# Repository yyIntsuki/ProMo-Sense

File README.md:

# ProMo-Sense

This repository is used for development and version control of ProMo-Sense.

### Overview
```bash
ProMo-Sense
├── hardware: hardware components development (audio module, code-lock)
├── raspberry: integration code with hardware components and database on Raspberry Pi (using Python)
├── web: web application code and functionalities including database (using Vite-React)
```

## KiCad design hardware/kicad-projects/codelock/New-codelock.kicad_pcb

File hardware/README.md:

# Raspberry

This folder is designated for hardware components such as their KiCad projects.

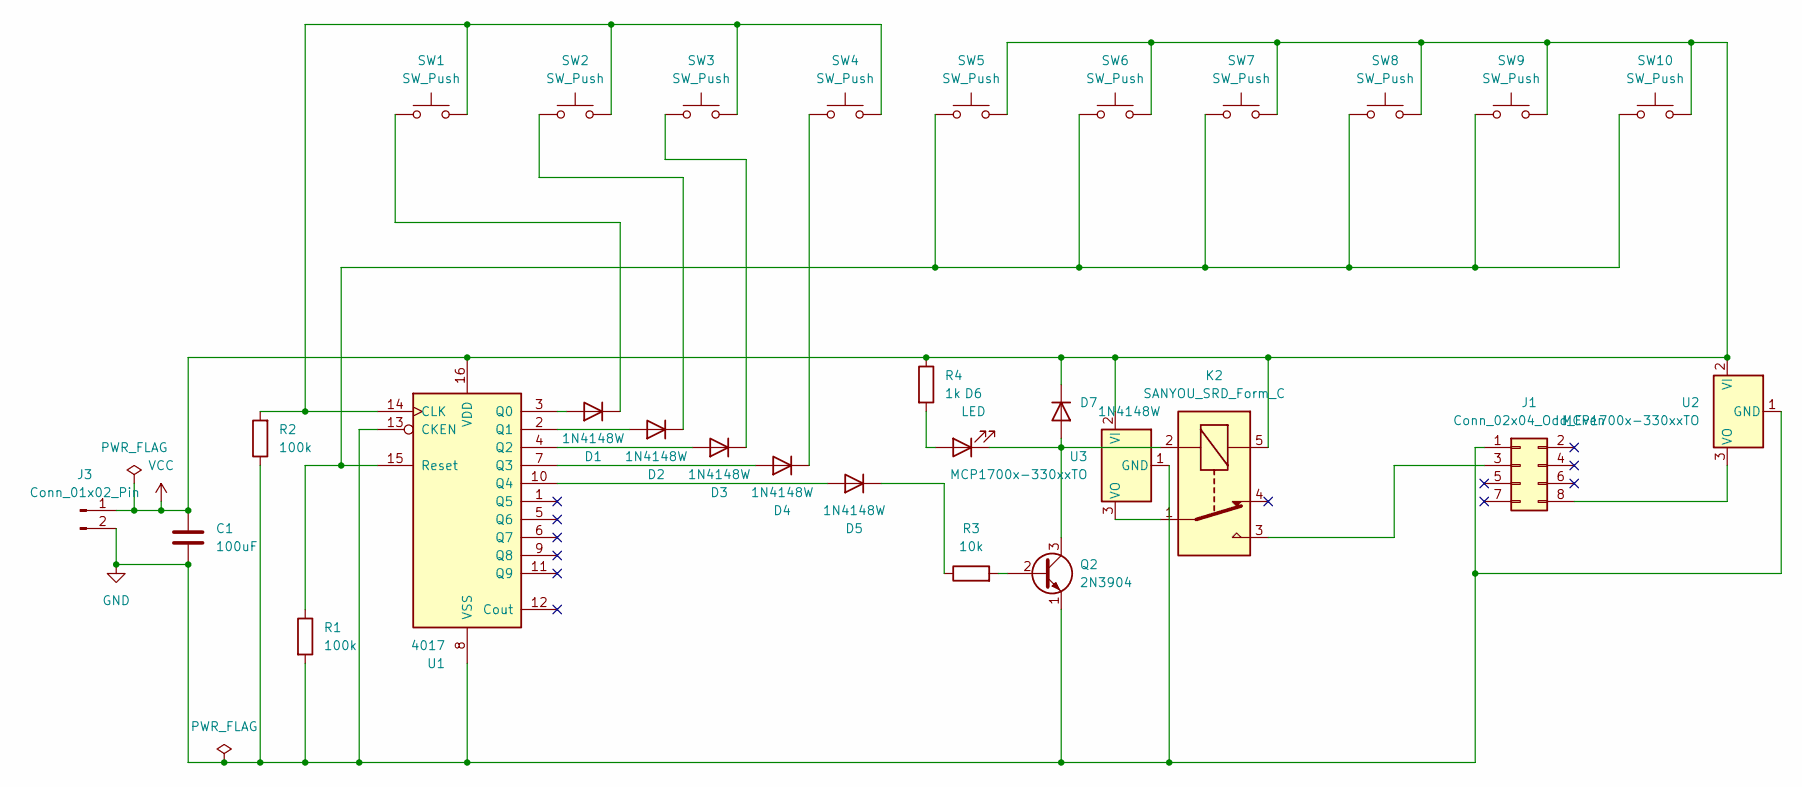
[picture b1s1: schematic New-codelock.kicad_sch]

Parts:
C1: 100uF; C_0805_2012Metric_Pad1.18x1.45mm_HandSolder
D1, D2, D3, D4, D5, D7: 1N4148W; D_SOD-123
D6: LED; LED_D5.0mm
J1: Conn_02x04_Odd_Even; PinSocket_2x04_P2.54mm_Vertical
J3: Conn_01x02_Pin; PinHeader_1x02_P2.54mm_Vertical
K2: SANYOU_SRD_Form_C; Relay_SPDT_SANYOU_SRD_Series_Form_C
Q2: 2N3904; TO-92_Inline
R1, R2: 100k; R_0805_2012Metric_Pad1.20x1.40mm_HandSolder
R3: 10k; R_0805_2012Metric_Pad1.20x1.40mm_HandSolder
R4: 1k; R_0805_2012Metric_Pad1.20x1.40mm_HandSolder
SW1, SW2, SW3, SW4, SW5, SW6, SW7, SW8, SW9, SW10: SW_Push; SW_PUSH_6mm
U1: 4017; CERDIP-16_W7.62mm_SideBrazed_LongPads_Socket
U2, U3: MCP1700x-330xxTO; TO-92_Inline

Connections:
GND: C1.2, J1.1, J3.2, Q2.1 (E), R1.2, R2.1, U1.8 (VSS), U1.13 (CKEN), U2.1 (GND), U3.1 (GND)
unnamed: D1.2 (A), U1.3 (Q0)
unnamed: D1.1 (K), SW1.1
unnamed: D2.2 (A), U1.2 (Q1)
unnamed: D2.1 (K), SW2.1
unnamed: D3.2 (A), U1.4 (Q2)
unnamed: D3.1 (K), SW3.1
unnamed: D4.2 (A), U1.7 (Q3)
unnamed: D4.1 (K), SW4.1
unnamed: D5.2 (A), U1.10 (Q4)
unnamed: D5.1 (K), R3.1
unnamed: D6.2 (A), R4.2
unnamed: D6.1 (K), D7.2 (A), K2.2, Q2.3 (C)
unnamed: J1.3, K2.3
unnamed: J1.8, U2.3 (VO)
unnamed: Q2.2 (B), R3.2
unnamed: R2.2, SW1.2, SW2.2, SW3.2, SW4.2, U1.14 (CLK)
unnamed: R1.1, SW5.1, SW6.1, SW7.1, SW8.1, SW9.1, SW10.1, U1.15 (Reset)
unnamed: K2.1, U3.3 (VO)
VCC: C1.1, D7.1 (K), J3.1, K2.5, R4.1, SW5.2, SW6.2, SW7.2, SW8.2, SW9.2, SW10.2, U1.16 (VDD), U2.2 (VI), U3.2 (VI)

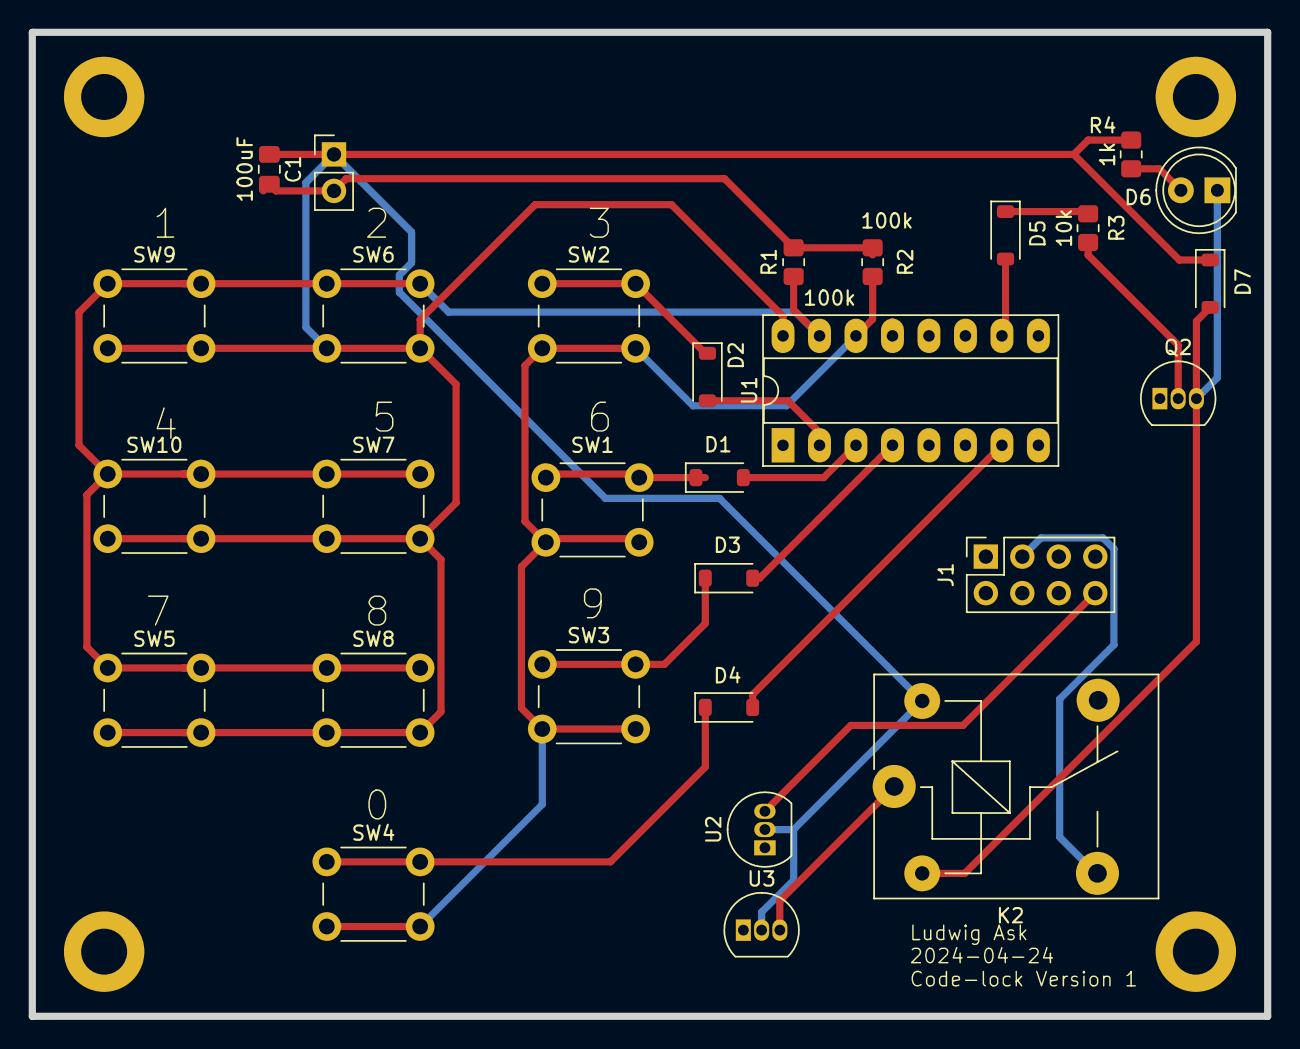
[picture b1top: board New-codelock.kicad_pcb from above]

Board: 2 copper layers, 86.0 x 68.5 mm, 29 parts (0 on the bottom side), 20 nets.

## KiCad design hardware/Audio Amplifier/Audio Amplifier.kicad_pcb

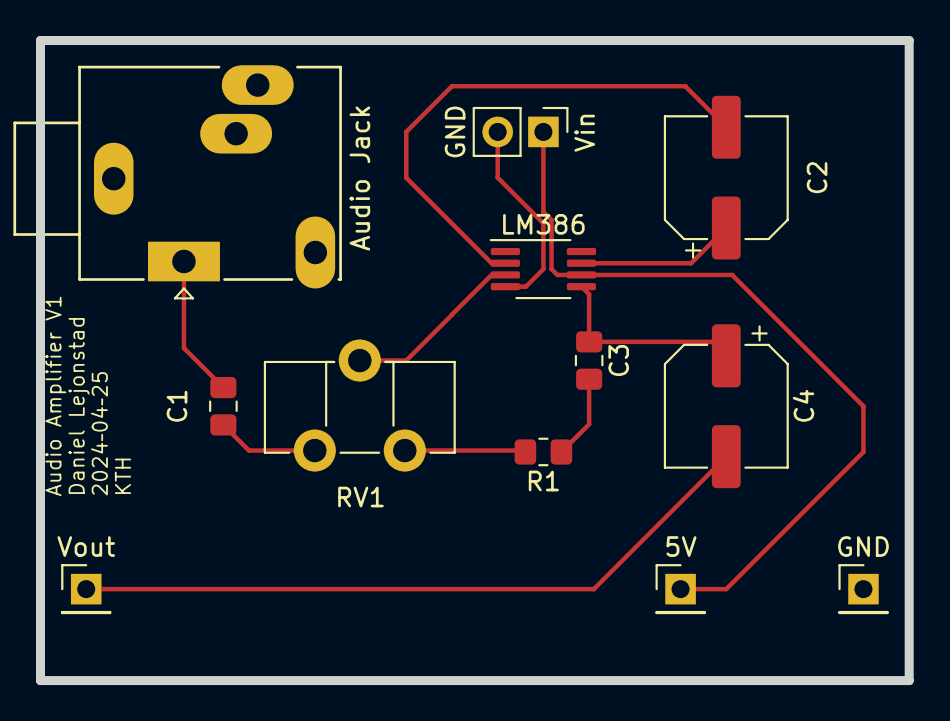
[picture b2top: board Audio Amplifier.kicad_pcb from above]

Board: 2 copper layers, 48.3 x 35.6 mm, 12 parts (0 on the bottom side), 10 nets.

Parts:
5V: 5V; PinHeader_1x01_P2.54mm_Vertical
Audio Jack: AudioJack; Jack_3.5mm_Ledino_KB3SPRS_Horizontal
C1: 0.22; C_0805_2012Metric_Pad1.18x1.45mm_HandSolder
C2: 47; CP_Elec_6.3x5.4
C3: 0.47; C_0805_2012Metric_Pad1.18x1.45mm_HandSolder
C4: 220; CP_Elec_6.3x5.4
GND: GND; PinHeader_1x01_P2.54mm_Vertical
LM386: LM386; MSOP-8_3x3mm_P0.65mm
R1: 10; R_0805_2012Metric_Pad1.20x1.40mm_HandSolder
RV1: 10k; Potentiometer_Piher_PT-10-H05_Horizontal
Vin: GND; PinHeader_1x02_P2.54mm_Vertical
Vout: Vout; PinHeader_1x01_P2.54mm_Vertical

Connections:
GND: Audio Jack.R, Audio Jack.S, GND.1, LM386.4 (GND), R1.2, RV1.3, Vin.2
unnamed: 5V.1, LM386.6 (V+), Vin.1
unnamed: Audio Jack.T, C1.1
unnamed: C1.2, RV1.1
unnamed: C3.1, C4.1, LM386.5
unnamed: C3.2, R1.1
unnamed: C4.2, Vout.1
unnamed: LM386.3 (+), RV1.2
unnamed: C2.2, LM386.2 (-)
unnamed: C2.1, LM386.7 (BYPASS)

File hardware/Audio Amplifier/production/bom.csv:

Designator,Footprint,Quantity,Value,LCSC Part #
5V,PinHeader_1x01_P2.54mm_Vertical,1,5V,
Audio Jack,Jack_3.5mm_Ledino_KB3SPRS_Horizontal,1,AudioJack,
C1,0805,1,0.22,
C2,CP_Elec_6.3x5.4,1,47,
C3,0805,1,0.47,
C4,CP_Elec_6.3x5.4,1,220,
GND,PinHeader_1x01_P2.54mm_Vertical,1,GND,
LM386,MSOP-8_3x3mm_P0.65mm,1,LM386,
R1,0805,1,10,
RV1,Potentiometer_Piher_PT-10-H05_Horizontal,1,10k,
Vin,PinHeader_1x02_P2.54mm_Vertical,1,GND,
Vout,PinHeader_1x01_P2.54mm_Vertical,1,Vout,

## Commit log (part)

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2024-04-12 added two folders for raspberry and web
2024-04-12 fixed incorrect folder readmes
2024-04-17 Started with the about page
    out page
2024-04-17 MinorChanges
    Minor changes
2024-04-17 Bilder på gruppmedlemmar
2024-04-17 tog bort oanvända filer
2024-04-17 minor change
    minor
2024-04-17 Flyttar alla filer till web folder
2024-04-17 flyttar alla filer till webb folder
2024-04-17 mm
    mm
2024-04-17 Daniels bild är uppe
2024-04-17 added style.css
2024-04-17 my minor change
    change
2024-04-17 added package for npm
2024-04-17 moved files from incorrect folder
2024-04-17 minor formatting on package json
2024-04-17 setup vue dev environment
2024-04-17 fixing issue with duplicate folders (1/2)
2024-04-17 fixing issue with duplicate folders (2/2)
2024-04-18 fixed an issue with building due to vue logo was removed
2024-04-18 react root
    reactRoot
2024-04-18 Update aboutTheGroupMembersView.jsx
    Salahs view
2024-04-18 completely re-built web structure to vite-react. cleaned up vue library and some other unnecessary files.
2024-04-18 updated with ali's changes from my previous commit.
2024-04-18 cleaned up a duplicate file.
2024-04-18 added a simple python script for motion sensor (commited from raspberry)
2024-04-18 refactored some code.
2024-04-19 Test
    Test
2024-04-19 reformatted some code
2024-04-19 modified css such that members is listed horizontally.
2024-04-19 updated gitignore for firebase
2024-04-19 configured firebase imports.
2024-04-19 added dark mode styling to about page.
2024-04-19 made import and exports more condensed.
2024-04-20 moved GoogleAuthProvider to firebase model instead.
2024-04-20 fixed typo; made css class naming consistent.
2024-04-20 fixed firebaseModel provider.
2024-04-20 reverted a test change from certain commit.
2024-04-20 fixed roles in about page being incorrect.
2024-04-21 added custom font.
2024-04-22 removed firestore dependency since we will not be using it.
2024-04-23 Added a login presenter, when you log in your email is saved in the firebase database
2024-04-23 My files
    bread
2024-04-23 Minor change
    Minor changes
2024-04-23 added header and footer navbars, and renamed some files. added CSS for all of them.
2024-04-23 added a way to direct to login page. and unified css for login page.
2024-04-23 added no-padding for body.
2024-04-23 removed unnecessary new-lines in css.
2024-04-23 deployed application on firebase.
2024-04-23 attempting to substitute index to work with our app.
2024-04-23 finally fixed build issue for firebase deploy.
2024-04-23 removed unnecessary package lock file...
2024-04-23 deleted public directory
    unnecessary
2024-04-24 Added some project info and updated css
    Added some project info and updated css
2024-04-24 Minor change
    Minor change
2024-04-24 added division line between footerNav items and corrected some class identifier names.
2024-04-24 Updated App so it can play audio
    Updated App so it can play audio
2024-04-24 Uploaded the pictures in imgbb.com which is a webbsite that saves images and gives you an URL that you could use. Now the pictures should be visible on the deployed webbsite
2024-04-24 Being able to choose audio
    Being able to choose audio
2024-04-24 Choose a song, logic if something plays
    Choose a song, logic if something plays
2024-04-24 added test button
    added test button
2024-04-24 Adjust volume added
    Adjust volume added
2024-04-25 added a gitignore for raspberry pi
2024-04-25 added a simple test program for database connection to firebase. also tested to import another file in python.
2024-04-25 Fixed login redirect so that now when you login, you are redirected to gmail to login and then back to the ProMoSence webbsite
2024-04-25 Minor changes imported the correct LoginRedirectApp
2024-04-25 updated sensor program with an initialization phase.
2024-04-25 restructured motion sensor a bit.
2024-04-25 cleaned up and restructred files. because we are not going to need to seperate files as the app is relatively small.
2024-04-25 added styling for contact buttons.
2024-04-26 added codelock source code.
2024-04-26 added audio amplifier source code.
2024-04-26 added some more mock-up options and data, improved app css.
2024-04-26 Added that audio will play on rasberry
    Added that audio will play on rasberry
2024-04-26 reverted changes to motionSensor
2024-04-26 reverted a minor change in the file.
2024-04-26 implemented an initial monitoring for motion to db
2024-04-26 reverted a change that did not work.
2024-04-26 set init status to db from rp.
2024-04-26 added ability to track running time of the program. this way, the web app can track if raspberry is off or has issues.
2024-04-27 imported getDabase from firebase/database. This is done to save data to the database,
2024-04-27 Login and sign out fixed, also saves data to firebase
    Fixed the login so that the user is only able to login when they are signed out. Also added some logic to handle signout. Lastly, integrated the user information to a realtime database, now we can se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
2024-04-27 increased timer interval to set on db to avoid consuming too much quota.
2024-04-27 adjusted code style to comply with python lint.
2024-04-27 adjusted some imports and gitignore for .DS_Store.
2024-04-27 cleaned up some code and dependencies.
2024-04-27 modified css styles for app.
2024-04-27 corrected some wording and adjusted css in app.
2024-04-28 Added set button and set up volume in firebase
    Added set button and set up volume in firebase
2024-04-28 Used correct const name of database from firebase model
    Used correct const name of database from firebase model
2024-04-28 merged app with my previous mock-up data (necessary for now) and improved app layout. formatted some code.
2024-04-28 fixed issue where volume would be in incorrect decimal forms.
2024-04-28 fixed such that previous changes changed how adjusting volume levels prevented abnormal values.
2024-04-29 Removed last name, since everyone that uses gmail does not need to have a last nam
2024-04-29 Changed select song to select sound
2024-04-29 added hover styling to clickables on header and footer.
2024-04-29 added more responsive padding to each page content.
2024-04-29 Fixed so the once u set to one volume it stays there even after refresh
    Fixed so the once u set to one volume it stays there even after refresh
2024-04-29 imlemented a userContext that works within the user session.
2024-04-29 migrated the login page functionalities directly to top nav bar.
2024-04-29 cleaned up unused login page and refactored all firebase related main functions into firebaseModel.
2024-04-29 added a simple text for users who are not logged in; as the web app app page should not be shown in that case.
2024-04-29 removed some unnecessary exports in firebase model.
2024-04-30 adjusted pin setup for motion sensor due to new raspberry case. I did some cable management and wiring.
2024-04-30 fixed typo
2024-04-30 Update README.md for raspberry dir
2024-04-30 implemented a fully mobile-ready layout for web app.
2024-04-30 added compressed and edited image links to about team page. should speed up the image load times significantly now.
2024-04-30 changed database rules for firebase real-time database. seems to be the culprit for resetting the rules before.
2024-05-02 implemented functionality to get and download media files from firebase storage for raspberry.
2024-05-02 moved raspberry source files to a src folder.
2024-05-02 added async behavior for set user in database function and corrected a path in comment for motion sensor doc.
2024-05-02 Fixed so we can upload files to firebase storage
    Fixed so we can upload files to firebase storage
2024-05-03 merged with css changes.
2024-05-03 fixed missing await keyword.
2024-05-03 adressed a critical issue where signInWithRedirect fails to work due to third party cookie policy.
2024-05-03 adjusted some unnecessary changes from before when attempted to fix issue in previous commit.
2024-05-03 changed styling for selection of audio sample on the web app.
2024-05-03 adjusted styling for footer in mobile portrait and landscape mode.
2024-05-03 fixed some margin issue with app in landscape mode; adjusted such that landscape mode would not touch the sides on a real phone.
2024-05-04 added more params that we would want for the app.
2024-05-04 adjusted lock-time input width.
2024-05-04 implemented temporary alert when submitting changes to database/storage.
2024-05-04 some major adjustment to how motion sensor works, such that the loop is no longer blocking.
2024-05-04 implemented audio playback for motion sensor detection. not finished with modularity, most execution are written in motion sensor file.
2024-05-05 improved pir initialization phase, adjusted time functions in utils.
2024-05-05 fixed so we can get data from motion sensor
    fixed so we can get data from motion sensor
2024-05-05 split functionalities to multiple modules, and implemented a main function to execute all parts of the ProMo-Sense.
2024-05-05 fixed some formatting.
2024-05-05 change to onValue
    change to onValue
2024-05-05 added default behavior for when some data that would not be shown before sensor intialization.
2024-05-05 audio program now selects randomly a file from user if not specified.
2024-05-05 added some indication to the console during program run in audio module.
2024-05-09 Activate the code lock manually works now, the data is saved in firebase. Same goes to the time the code lock is locked, the time chosen by the user is saved in firebase
2024-05-10 Set up for sample in firebase done
    Set up for sample in firebase done
2024-05-10 Added sample persistence
    Added sample persistence
2024-05-11 disabled audio testing function, and changed variable to set for sample file name in db.
2024-05-11 readjusted imports between files such that they can use each others' global variables.
2024-05-12 implemented a listen for changes function for user, sample and volume. and parallelized motion sensor as thread.
2024-05-12 adjusted get audio samples function.
2024-05-12 raspberry is now able to keep track of user, sample and volume changes.
2024-05-13 made sure file names are in the firebase
    made sure file names are in the firebase
2024-05-13 cleared up some unnecessary dependencies.
2024-05-13 updated database path for chosen_sound in raspberry.
2024-05-13 changed set to update for setManualLock.
2024-05-13 changed time to be unix time seconds instead for code lock.
2024-05-13 raspberry is now able to disable motion sensor if lock time is greater than current time.
2024-05-13 cleaned up some clutters in console logs.
2024-05-13 removed unused variable.
2024-05-13 added missing dependencies in useEffect.
2024-05-14 implemented code for code-lock program.
2024-05-14 Fixed a count down for the time the user choses to lock ProMoSence. Activate and decactivate buttons are now visible so that the user could see if the code lock is activated or not. Lastly, if the co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
2024-05-14 Minor changes
2024-05-14 Fixed persistance issue, now when website is refreshed same lock time will be seen. The status time is now directly fetched from the firebase database.
2024-05-14 restructured hardware folders, uploaded an initial code for trying to use ESP8266 WiFi module for the code-lock.
2024-05-14 adjusted some arduino code.
2024-05-14 adjusted condition for notifying that the code-lock is active.
2024-05-14 Fixed persiatnce isuues, change the lock time value that is saved in firebase to an integer
2024-05-15 Minor errors fixed
2024-05-15 Minor changes, sound is now changable and not only 100%. Filename is now shown instaed of sound 1 and so on
2024-05-16 updated some stuff.
2024-05-16 updated some formatting.
2024-05-16 Trimmed sound to max 15 words
2024-05-16 Minor changes, now the code lock is only activated when you press actiavte and not not apply when choosing time
2024-05-16 fixed issue with choosing sample altered filename.
2024-05-16 removed the requirement in file path to require user id for now.
2024-05-16 reverted some change.
2024-05-16 Minor changes,status of code lock is now updated.
2024-05-16 adjusted daniel's email in about page; adjusted project descriptions.
